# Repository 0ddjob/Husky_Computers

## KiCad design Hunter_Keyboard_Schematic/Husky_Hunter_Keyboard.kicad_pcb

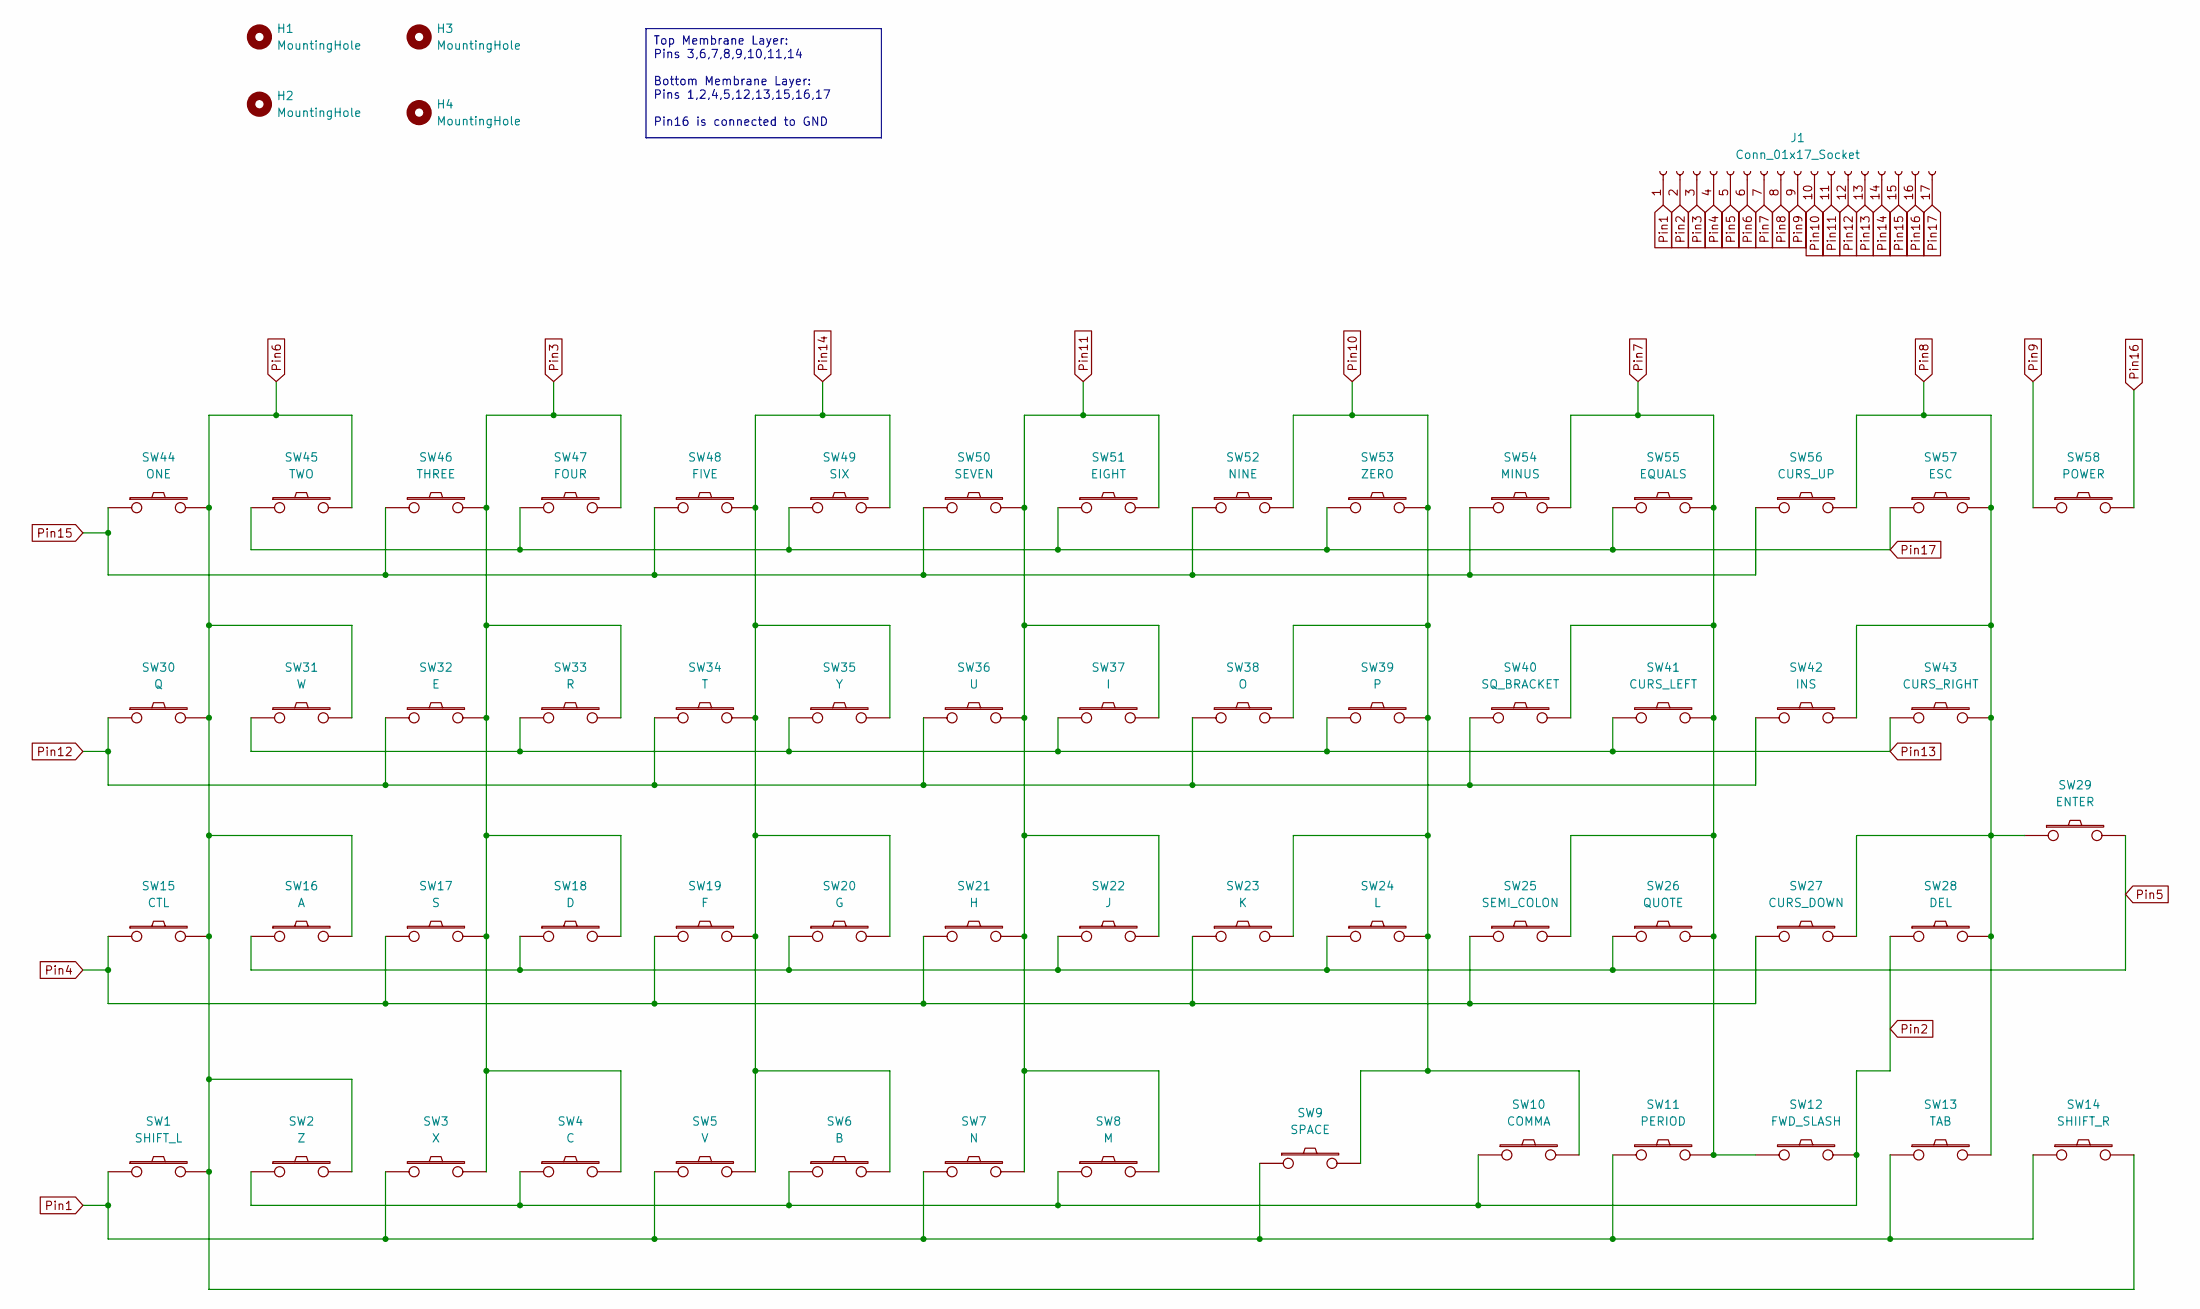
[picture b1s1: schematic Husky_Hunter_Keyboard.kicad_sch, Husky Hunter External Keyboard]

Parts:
H1, H2, H3, H4: MountingHole; MountingHole_3.2mm_M3_Pad
J1: Conn_01x17_Socket; PinSocket_1x17_P2.54mm_Horizontal
SW1: SHIFT_L; SW_Cherry_MX_1.00u_PCB
SW2: Z; SW_Cherry_MX_1.00u_PCB
SW3: X; SW_Cherry_MX_1.00u_PCB
SW4: C; SW_Cherry_MX_1.00u_PCB
SW5: V; SW_Cherry_MX_1.00u_PCB
SW6: B; SW_Cherry_MX_1.00u_PCB
SW7: N; SW_Cherry_MX_1.00u_PCB
SW8: M; SW_Cherry_MX_1.00u_PCB
SW9: SPACE; SW_Cherry_MX_1.00u_PCB
SW10: COMMA; SW_Cherry_MX_1.00u_PCB
SW11: PERIOD; SW_Cherry_MX_1.00u_PCB
SW12: FWD_SLASH; SW_Cherry_MX_1.00u_PCB
SW13: TAB; SW_Cherry_MX_1.00u_PCB
SW14: SHIIFT_R; SW_Cherry_MX_1.00u_PCB
SW15: CTL; SW_Cherry_MX_1.00u_PCB
SW16: A; SW_Cherry_MX_1.00u_PCB
SW17: S; SW_Cherry_MX_1.00u_PCB
SW18: D; SW_Cherry_MX_1.00u_PCB
SW19: F; SW_Cherry_MX_1.00u_PCB
SW20: G; SW_Cherry_MX_1.00u_PCB
SW21: H; SW_Cherry_MX_1.00u_PCB
SW22: J; SW_Cherry_MX_1.00u_PCB
SW23: K; SW_Cherry_MX_1.00u_PCB
SW24: L; SW_Cherry_MX_1.00u_PCB
SW25: SEMI_COLON; SW_Cherry_MX_1.00u_PCB
SW26: QUOTE; SW_Cherry_MX_1.00u_PCB
SW27: CURS_DOWN; SW_Cherry_MX_1.00u_PCB
SW28: DEL; SW_Cherry_MX_1.00u_PCB
SW29: ENTER; SW_Cherry_MX_1.00u_PCB
SW30: Q; SW_Cherry_MX_1.00u_PCB
SW31: W; SW_Cherry_MX_1.00u_PCB
SW32: E; SW_Cherry_MX_1.00u_PCB
SW33: R; SW_Cherry_MX_1.00u_PCB
SW34: T; SW_Cherry_MX_1.00u_PCB
SW35: Y; SW_Cherry_MX_1.00u_PCB
SW36: U; SW_Cherry_MX_1.00u_PCB
SW37: I; SW_Cherry_MX_1.00u_PCB
SW38: O; SW_Cherry_MX_1.00u_PCB
SW39: P; SW_Cherry_MX_1.00u_PCB
SW40: SQ_BRACKET; SW_Cherry_MX_1.00u_PCB
SW41: CURS_LEFT; SW_Cherry_MX_1.00u_PCB
SW42: INS; SW_Cherry_MX_1.00u_PCB
SW43: CURS_RIGHT; SW_Cherry_MX_1.00u_PCB
SW44: ONE; SW_Cherry_MX_1.00u_PCB
SW45: TWO; SW_Cherry_MX_1.00u_PCB
SW46: THREE; SW_Cherry_MX_1.00u_PCB
SW47: FOUR; SW_Cherry_MX_1.00u_PCB
SW48: FIVE; SW_Cherry_MX_1.00u_PCB
SW49: SIX; SW_Cherry_MX_1.00u_PCB
SW50: SEVEN; SW_Cherry_MX_1.00u_PCB
SW51: EIGHT; SW_Cherry_MX_1.00u_PCB
SW52: NINE; SW_Cherry_MX_1.00u_PCB
SW53: ZERO; SW_Cherry_MX_1.00u_PCB
SW54: MINUS; SW_Cherry_MX_1.00u_PCB
SW55: EQUALS; SW_Cherry_MX_1.00u_PCB
SW56: CURS_UP; SW_Cherry_MX_1.00u_PCB
SW57: ESC; SW_Cherry_MX_1.00u_PCB
SW58: POWER; Switch_Tactile_6mm

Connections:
Pin1: J1.1, SW1.1, SW3.1, SW5.1, SW7.1, SW9.1, SW11.1, SW13.1, SW14.1
Pin2: J1.2, SW2.1, SW4.1, SW6.1, SW8.1, SW10.1, SW12.2, SW28.1
Pin3: J1.3, SW3.2, SW4.2, SW17.2, SW18.2, SW32.2, SW33.2, SW46.2, SW47.2
Pin4: J1.4, SW15.1, SW17.1, SW19.1, SW21.1, SW23.1, SW25.1, SW27.1
Pin5: J1.5, SW16.1, SW18.1, SW20.1, SW22.1, SW24.1, SW26.1, SW29.2
Pin6: J1.6, SW1.2, SW2.2, SW14.2, SW15.2, SW16.2, SW30.2, SW31.2, SW44.2, SW45.2
Pin7: J1.7, SW11.2, SW12.1, SW25.2, SW26.2, SW40.2, SW41.2, SW54.2, SW55.2
Pin8: J1.8, SW13.2, SW27.2, SW28.2, SW29.1, SW42.2, SW43.2, SW56.2, SW57.2
Pin9: J1.9, SW58.1
Pin10: J1.10, SW9.2, SW10.2, SW23.2, SW24.2, SW38.2, SW39.2, SW52.2, SW53.2
Pin11: J1.11, SW7.2, SW8.2, SW21.2, SW22.2, SW36.2, SW37.2, SW50.2, SW51.2
Pin12: J1.12, SW30.1, SW32.1, SW34.1, SW36.1, SW38.1, SW40.1, SW42.1
Pin13: J1.13, SW31.1, SW33.1, SW35.1, SW37.1, SW39.1, SW41.1, SW43.1
Pin14: J1.14, SW5.2, SW6.2, SW19.2, SW20.2, SW34.2, SW35.2, SW48.2, SW49.2
Pin15: J1.15, SW44.1, SW46.1, SW48.1, SW50.1, SW52.1, SW54.1, SW56.1
Pin16: J1.16, SW58.2
Pin17: J1.17, SW45.1, SW47.1, SW49.1, SW51.1, SW53.1, SW55.1, SW57.1

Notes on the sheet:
Top Membrane Layer: Pins 3,6,7,8,9,10,11,14 Bottom Membrane Layer: Pins 1,2,4,5,12,13,15,16,17 Pin16 is connected to GND

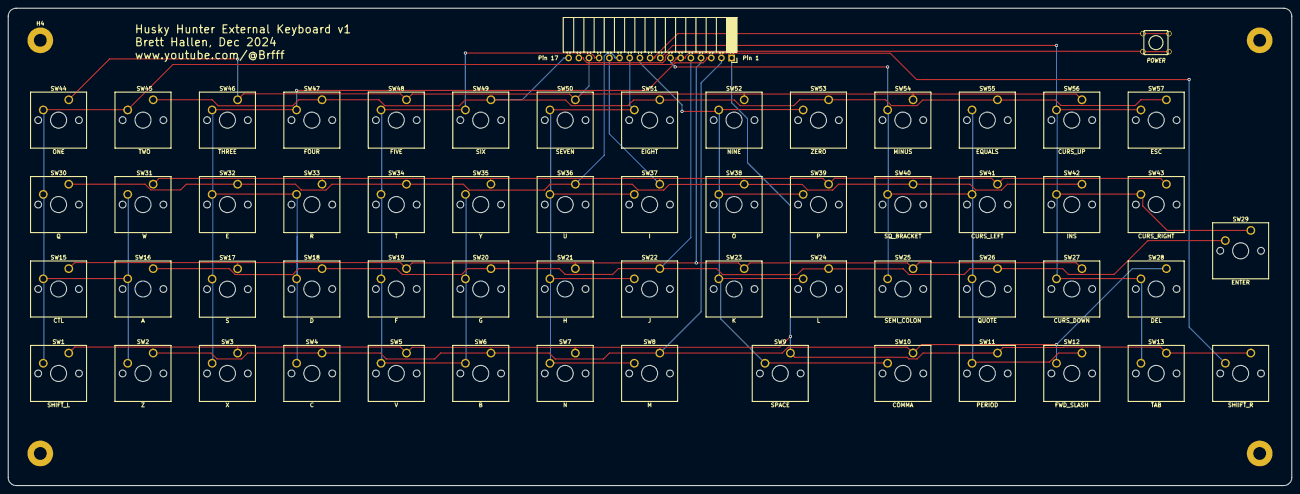
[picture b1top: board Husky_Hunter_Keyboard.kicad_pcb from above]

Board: 2 copper layers, 320.0 x 119.0 mm, 63 parts (0 on the bottom side), 17 nets.

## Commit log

2024-07-21 Replacement keyboard initial design
2024-07-21 Converted logo file
2024-07-22 Some cleanup
2024-07-22 Ignore MacOS junk files
2024-12-27 PCB design created for testing
2024-12-27 Added schematic PDF/PCB image
